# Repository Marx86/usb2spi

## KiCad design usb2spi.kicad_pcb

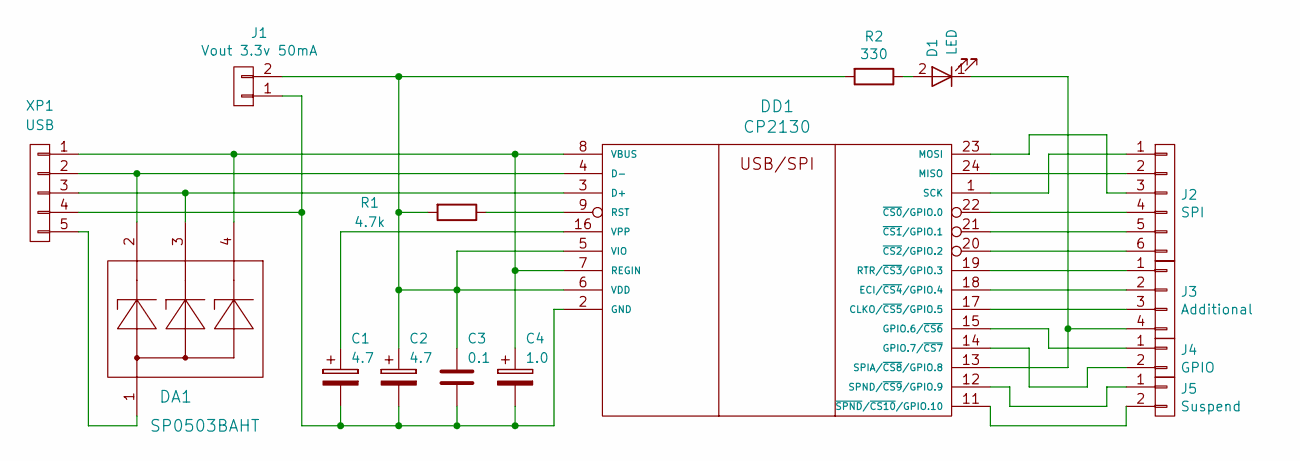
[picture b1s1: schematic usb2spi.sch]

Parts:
C1, C2: 4.7; CP_Radial_D5.0mm_P2.00mm
C3: 0.1; C_0805
C4: 1.0; C_0805
D1: LED; LED_1206
DA1: SP0503BAHT; SOT-143
DD1: CP2130; QFN-24_4x4mm_Pitch0.5mm_NoMask
J1: Vout 3.3v 50mA; Pin_Header_Straight_1x02_Pitch2.54mm
J2: SPI; Pin_Header_Straight_1x06_Pitch2.54mm
J3: Additional; Pin_Header_Straight_1x04_Pitch2.54mm
J4: GPIO; Pin_Header_Straight_1x02_Pitch2.54mm
J5: Suspend; Pin_Header_Straight_1x02_Pitch2.54mm
R1: 4.7k; R_0805
R2: 330; R_0805
XP1: USB; USB_B

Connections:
unnamed: C1.1, DD1.16 (VPP)
unnamed: C1.2, C2.2, C3.2, C4.2, DD1.2 (GND), J1.1, XP1.4
unnamed: C2.1, C3.1, DD1.5 (VIO), DD1.6 (VDD), J1.2, R1.2, R2.2
unnamed: C4.1, DA1.4, DD1.7 (REGIN), DD1.8 (VBUS), XP1.1
unnamed: D1.1 (K), DD1.13 (SPIA/~CS8~/GPIO.8), J3.4
unnamed: D1.2 (A), R2.1
unnamed: DA1.1, XP1.5
unnamed: DA1.2, DD1.4 (D-), XP1.2
unnamed: DA1.3, DD1.3 (D+), XP1.3
unnamed: DD1.1 (SCK), J2.1
unnamed: DD1.9 (RST), R1.1
unnamed: DD1.11 (~SPND~/~CS10~/GPIO.10), J5.2
unnamed: DD1.12 (SPND/~CS9~/GPIO.9), J5.1
unnamed: DD1.14 (GPIO.7/~CS7), J4.2
unnamed: DD1.15 (GPIO.6/~CS6), J4.1
unnamed: DD1.17 (CLKO/~CS5~/GPIO.5), J3.3
unnamed: DD1.18 (ECI/~CS4~/GPIO.4), J3.2
unnamed: DD1.19 (RTR/~CS3~/GPIO.3), J3.1
unnamed: DD1.20 (~CS2~/GPIO.2), J2.6
unnamed: DD1.21 (~CS1~/GPIO.1), J2.5
unnamed: DD1.22 (~CS0~/GPIO.0), J2.4
unnamed: DD1.23 (MOSI), J2.3
unnamed: DD1.24 (MISO), J2.2

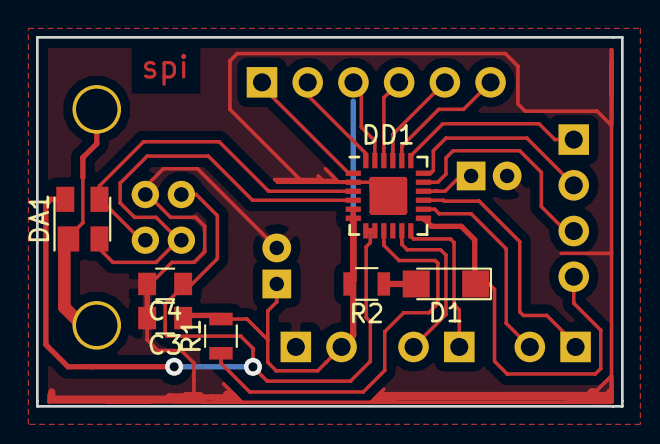
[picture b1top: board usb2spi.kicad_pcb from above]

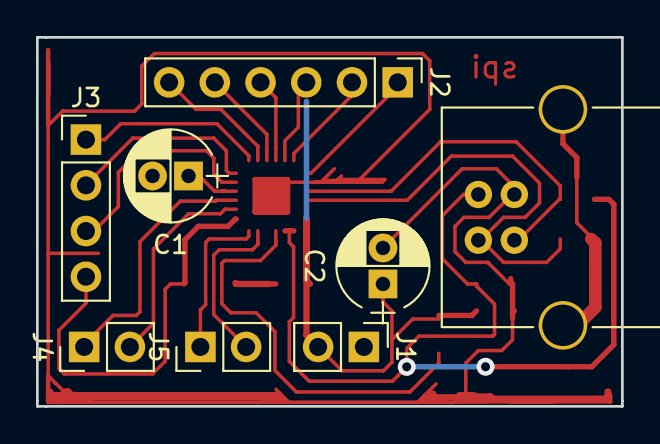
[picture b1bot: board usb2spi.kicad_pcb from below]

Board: 2 copper layers, 32.5 x 20.5 mm, 15 parts (8 on the bottom side), 23 nets.

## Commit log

2018-03-21 Add project files
2018-05-17 Trace PCB
2018-12-26 Fix PCB
